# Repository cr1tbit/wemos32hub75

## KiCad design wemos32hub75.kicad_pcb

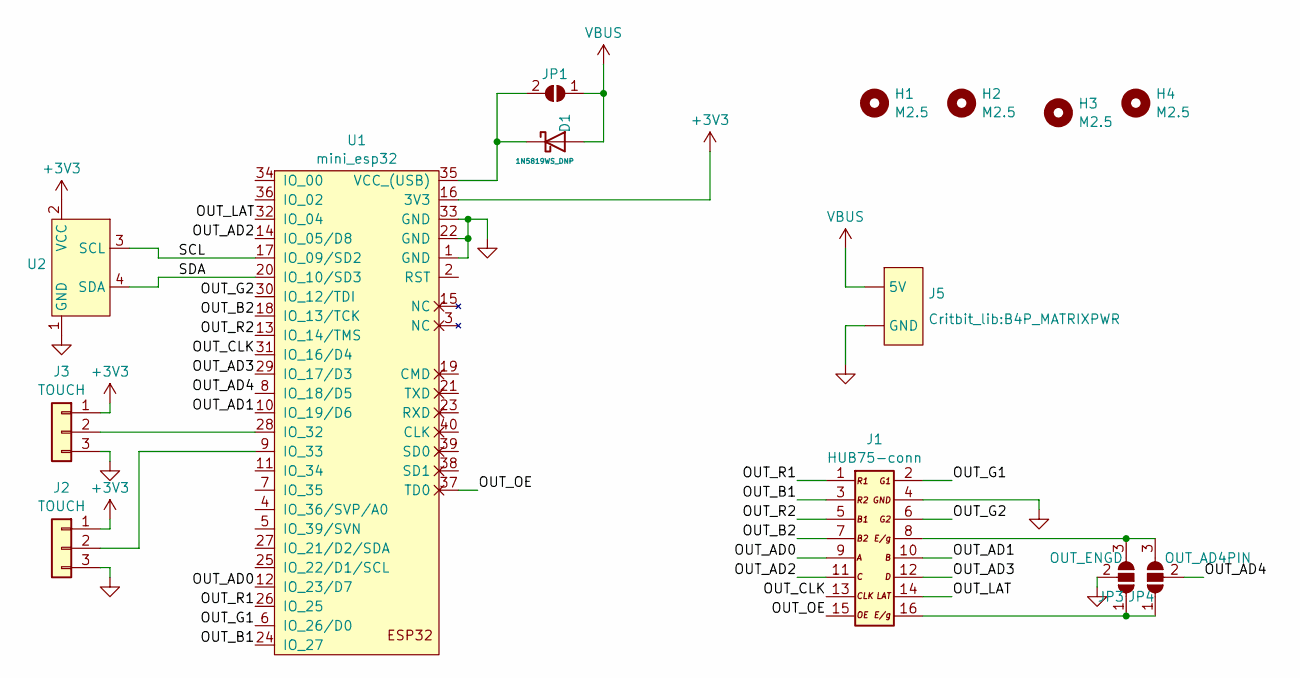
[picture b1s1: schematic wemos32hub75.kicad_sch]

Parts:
D1: 1N5819WS_DNP; D_SMA; LCSC C191023
H1, H2, H3, H4: M2.5; MountingHole_2.7mm_M2.5
J1: HUB75-conn; IDC-Header_2x08_P2.54mm_Vertical
J2, J3: TOUCH; PinHeader_1x03_P2.54mm_Vertical
J5: B4P_MATRIXPWR
JP1: BYPASS_VBUS; SolderJumper-2_P1.3mm_Open_TrianglePad1.0x1.5mm
JP3: OUT_ENGD; 3jumper
JP4: OUT_AD4PIN; 3jumper
U1: mini_esp32; ESP32_mini
U2: OLED_4Pin

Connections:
+3V3: J2.1, J3.1, U1.16 (3V3), U2.2 (VCC)
/OUT_AD0: J1.9, U1.12 (IO_23/D7)
/OUT_AD1: J1.10, U1.10 (IO_19/D6)
/OUT_AD2: J1.11, U1.14 (IO_05/D8)
/OUT_AD3: J1.12, U1.29 (IO_17/D3)
/OUT_AD4: JP4.2 (C), U1.8 (IO_18/D5)
/OUT_B1: J1.3, U1.24 (IO_27)
/OUT_B2: J1.7, U1.18 (IO_13/TCK)
/OUT_CLK: J1.13, U1.31 (IO_16/D4)
/OUT_G1: J1.2, U1.6 (IO_26/D0)
/OUT_G2: J1.6, U1.30 (IO_12/TDI)
/OUT_LAT: J1.14, U1.32 (IO_04)
/OUT_OE: J1.15, U1.37 (TD0)
/OUT_R1: J1.1, U1.26 (IO_25)
/OUT_R2: J1.5, U1.13 (IO_14/TMS)
/SCL: U1.17 (IO_09/SD2), U2.3 (SCL)
/SDA: U1.20 (IO_10/SD3), U2.4 (SDA)
GND: J1.4, J2.3, J3.3, J5.GND, JP3.2 (C), U1.1 (GND), U1.22 (GND), U1.33 (GND), U2.1 (GND)
unnamed: D1.1 (K), JP1.2 (B), U1.35 (VCC_(USB))
unnamed: J1.8, JP3.3 (B), JP4.3 (B)
unnamed: J1.16, JP3.1 (A), JP4.1 (A)
unnamed: J2.2, U1.9 (IO_33)
unnamed: J3.2, U1.28 (IO_32)
VBUS: D1.2 (A), J5.5V, JP1.1 (A)

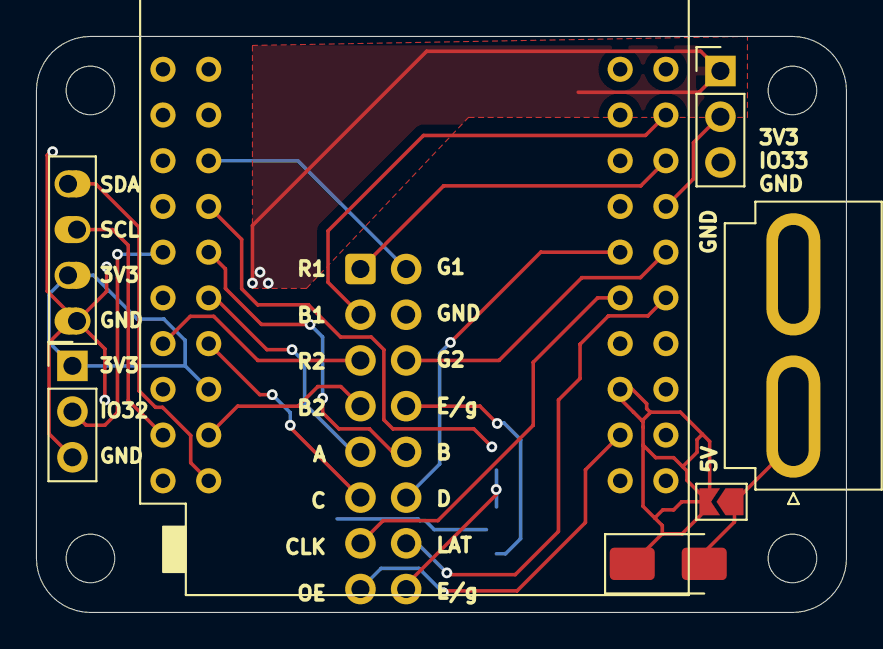
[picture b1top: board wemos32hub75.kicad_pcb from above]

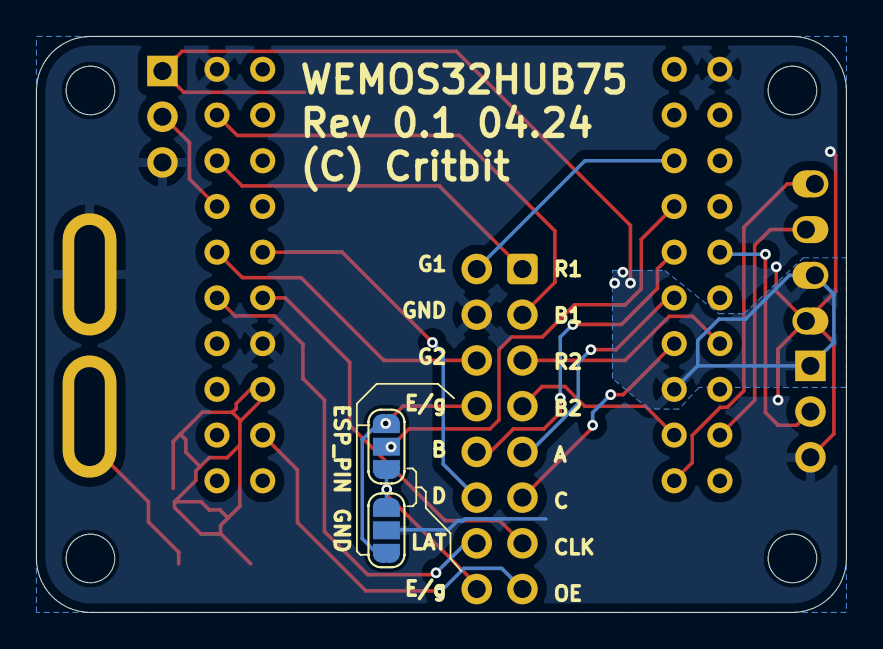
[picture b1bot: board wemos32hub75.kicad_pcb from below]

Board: 2 copper layers, 45.0 x 32.0 mm, 14 parts (2 on the bottom side), 24 nets.

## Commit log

2024-04-09 add files, pre gerbers
2024-04-09 add gerber
2024-11-17 add schematic
